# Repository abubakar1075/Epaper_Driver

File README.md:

# CanvasBT — EPaper BLE Image Transfer System

An end-to-end, practical reference for sending images to a 6‑color e‑paper display over Bluetooth Low Energy (BLE). This repo combines:
- Flutter mobile app (select/process image, send over BLE)
- ESP32/Arduino firmware (receive, persist, and render to e‑paper)
- Python tools (desktop image conversion and BLE utilities)

## Educational Intent

This is a personal, non‑commercial project published publicly to help engineers and learners understand mobile ↔ BLE ↔ embedded firmware ↔ e‑paper display integration. It focuses on real constraints: BLE throughput, MTU/chunking, limited RAM, image quantization, and e‑paper refresh behavior.

## What You’ll Learn

- Designing a BLE data transfer flow from mobile to microcontroller
- Handling chunking, buffering, acknowledgments, and integrity checks
- Converting images to a 6‑color e‑paper format (quantization + optional dithering)
- Structuring firmware for display initialization, frame buffer handling, and refresh sequencing
- Organizing a multi‑component system repo for reproducibility

## System Overview

Flutter App → (BLE) → ESP32 Firmware → (SPI/GPIO) → 6‑Color E‑Paper Display

Typical workflow:
1. Choose an image in the Flutter app
2. Enhance and quantize to hardware palette (optionally dither)
3. Pack pixels and transfer over BLE in chunks
4. ESP32 reassembles the image payload and persists if needed
5. ESP32 renders to e‑paper and triggers a refresh

## Repository Structure

- [Flutter/](Flutter/) — Mobile app with all UI + BLE + image logic
	- Core files: [lib/main.dart](Flutter/lib/main.dart), [lib/ble_manager.dart](Flutter/lib/ble_manager.dart), [lib/image_processor.dart](Flutter/lib/image_processor.dart)
	- Platforms: [android/](Flutter/android/), [ios/](Flutter/ios/), [windows/](Flutter/windows/), [linux/](Flutter/linux/), [macos/](Flutter/macos/), [web/](Flutter/web/)
	- Assets/examples: [Framepic/](Framepic/), [SamplePics/](SamplePics/), [EmulatorScreenshots/](EmulatorScreenshots/)
- [Arduino/Spectra6/](Arduino/Spectra6/) — ESP32 firmware and display drivers
	- Key files: [Spectra6.ino](Arduino/Spectra6/Spectra6.ino), [BLE.cpp](Arduino/Spectra6/BLE.cpp), [SPICom.cpp](Arduino/Spectra6/SPICom.cpp), [W21.cpp](Arduino/Spectra6/W21.cpp)
	- Build artifacts (example boards): [build/esp32.esp32.dfrobot_firebeetle2_esp32e/](Arduino/Spectra6/build/esp32.esp32.dfrobot_firebeetle2_esp32e/)
- [Python/](Python/) — Desktop tools: [epd_image_tool.py](Python/epd_image_tool.py), [epd_image_tool_ble.py](Python/epd_image_tool_ble.py)
- Documentation: [USER_MANUAL.md](USER_MANUAL.md), project notes in [.github/copilot-instructions.md](.github/copilot-instructions.md)

## Hardware Requirements

- ESP32 development board (tested on FireBeetle2 ESP32‑E and similar)
- 6‑color e‑paper display, 800×480 (landscape)
- SPI wiring: MOSI, SCLK, CS; control pins: DC, RST, BUSY; power: VCC, GND
- Optional touch/wake input

Tip: Pin mapping varies by display/module; check the firmware for pin defines and adapt wiring accordingly.

### Wiring & Connections

SPI and control signals required:

- Data/Clock: MOSI, SCLK
- Select: CS
- Control: DC (data/command), RST (reset), BUSY (controller busy)
- Power: VCC, GND

Example pin mapping template (fill with your board pins):

| Signal | ESP32 Pin | Notes |
|--------|-----------|-------|
| MOSI   | GPIO XX   | SPI data out |
| SCLK   | GPIO XX   | SPI clock |
| CS     | GPIO XX   | Chip select |
| DC     | GPIO XX   | Data/Command select |
| RST    | GPIO XX   | Hardware reset |
| BUSY   | GPIO XX   | Display busy (input to ESP32) |
| VCC    | 3V3       | Stable 3.3V |
| GND    | GND       | Common ground |

ESD and power tips:
- Keep SPI lines short and tidy; use ground reference next to signal lines where possible.
- Ensure 3.3V supply is robust; brownouts cause BLE drops or partial refreshes.
- Use level‑compatible displays; do not drive 5V logic into the panel.

## Software Requirements

- Flutter SDK (stable), Android Studio or VS Code
- Android phone recommended for BLE testing
- Arduino IDE with ESP32 board support; ArduinoBLE library
- Python 3.9+ (virtual environment recommended)

## Getting Started

### Flutter App

```bash
cd Flutter
flutter pub get
flutter run
```

Notes:
- Requires a BLE‑capable Android device connected via USB (or emulator with suitable BLE proxies).
- The app scans for devices with “EPD” in the advertisement name.

Quick architecture diagram:

```
┌────────────┐      BLE      ┌──────────────┐    SPI/GPIO    ┌─────────────────┐
│  Flutter   │ ───────────▶  │   ESP32      │ ─────────────▶ │  E‑Paper Panel  │
│   (App)    │ ◀───────────  │  (Firmware)  │ ◀───────────── │  (6‑Color, 800×480)
└────────────┘  Status/ACK   └──────────────┘   Busy/Control └─────────────────┘
```

### Arduino Firmware (ESP32)

1. Open the firmware in Arduino IDE: [Arduino/Spectra6/Spectra6.ino](Arduino/Spectra6/Spectra6.ino)
2. Install and select your ESP32 board package.
3. Ensure required libraries (ArduinoBLE, SPI, FS/SPIFFS) are available.
4. Build and upload to your ESP32.

After flashing:
- The device advertises over BLE (e.g., name includes “EPD”).
- Battery percentage is sent on connection.
- Deep sleep is used for low power; touch wake is supported.

### Python Tools (Optional/Desktop)

```bash
cd Python
python epd_image_tool.py --help
python epd_image_tool_ble.py --help
```

Examples:

```bash
# Standalone image conversion
python epd_image_tool.py --input SamplePics/photo.jpg --output out.bin

# BLE transfer from desktop (development aid)
python epd_image_tool_ble.py --file out.bin
```

## Display + Image Processing

- Display resolution: 800×480
- Pixels packed at 2 pixels per byte (palette index nibble pairs)
- Optional 180° rotation supported for orientation

Hardware palette (critical for compatibility):

```dart
static const List<ColorMap> hwPalette = [
	ColorMap(0x00, Color.fromRGBO(0, 0, 0, 1)),       // Black
	ColorMap(0xFF, Color.fromRGBO(255, 255, 255, 1)), // White  
	ColorMap(0xFC, Color.fromRGBO(255, 255, 0, 1)),   // Yellow
	ColorMap(0xE0, Color.fromRGBO(210, 0, 0, 1)),     // Red
	ColorMap(0x03, Color.fromRGBO(0, 0, 180, 1)),     // Blue
	ColorMap(0x1C, Color.fromRGBO(0, 150, 0, 1)),     // Green
];
```

Pipeline: Load → Enhance (brightness/contrast/saturation) → Resize (fit/stretch) → Quantize to 6 colors (optional Floyd‑Steinberg) → Pack pixels → Optional rotation → BLE transfer.

### Image Packing Format

- Two pixels per byte: `hi_nibble = pixel0_index`, `lo_nibble = pixel1_index`.
- Palette index must match the hardware palette order shown above.
- Row ordering follows the chosen orientation; rotation is applied pre‑transfer when enabled.

## BLE Protocol

- Service: Nordic UART `6E400001-B5A3-F393-E0A9-E50E24DCCA9E`
- Transfer types: `0x10` image, `0x20` OTA update
- Handshake: 4‑byte size header → ACK → chunked data
- Acknowledgments: `0x01` (size received), `0x02` (progress), `0x03` (complete), `0xFF` (error)
- Battery status: `0xB0` + percentage byte on connection
- Chunk size: 480 bytes (optimized for MTU and reliability)

Device discovery: the app scans for advertisements containing “EPD”.

### Packet/Handshake Details

Header exchange (image or OTA):
- Mobile sends 4‑byte size header (little‑endian length of payload) and transfer type byte (`0x10` image, `0x20` OTA).
- ESP32 replies with ACK `0x01` to confirm size reception.

Chunk transfer:
- Mobile streams payload in 480‑byte chunks.
- ESP32 issues periodic progress ACK `0x02` (implementation‑dependent cadence).
- On completion, ESP32 replies `0x03` or `0xFF` on error.

Battery status:
- On connection, ESP32 sends `0xB0` followed by a single percentage byte.

Recommended reliability notes:
- If MTU is smaller or unstable, reduce chunk size or increase ACK cadence.
- Consider adding sequence numbers and CRC in future (see Roadmap) for stronger integrity.

### Transfer Flow (ASCII)

```
App                                  ESP32
───                                  ────
Connect BLE  ───────────────────────▶ Advertise "EPD"
Receive 0xB0% ◀────────────────────── Battery status
Send header(size,type) ─────────────▶
					 ◀────────────── 0x01 (size ACK)
Send chunks (480B × N) ─────────────▶
					 ◀────────────── 0x02 (progress)
End of chunks ──────────────────────▶
					 ◀────────────── 0x03 (complete) or 0xFF (error)
```

OTA follows the same flow with type `0x20`, writing to firmware/image storage as defined in the ESP32 code.

## App Architecture & State

- Monolithic learning app with UI in [lib/main.dart](Flutter/lib/main.dart)
- BLE communication handled in [lib/ble_manager.dart](Flutter/lib/ble_manager.dart)
- Image processing in [lib/image_processor.dart](Flutter/lib/image_processor.dart)
- `setState()` used for state updates; BLE connection state tracked with timers
- Image library cached in memory and persisted via JSON/local storage
- Gestures: pan/zoom/rotate for precise framing

### UI/UX Flow Chart (Simplified)

```
[Launch]
	│
	├─▶ [Scan BLE] ─▶ [Select Device] ─▶ [Connect]
	│                                  │
	│                                  └─▶ [Battery %] overlay
	│
	├─▶ [Pick Image] ─▶ [Frame (pan/zoom/rotate)] ─▶ [Enhance]
	│                                                     │
	│                                                     └─▶ [Quantize + Pack]
	│                                                                     │
	└────────────────────────────────────────────────────────────────────▶ [Send]
																								  │
																								  └─▶ [Progress + Speed]
																											│
																											└─▶ [Complete → Refresh]
```

## Performance & Debugging

- High‑speed BLE: tuned chunk size (480 bytes) and batched ACKs
- Background isolates for image conversion to keep UI responsive
- Extensive console logging across Flutter and Arduino
- Real‑time transfer speed display during BLE operations
- Automatic reconnection attempts on disconnection

### Tips
- Enable verbose logs in both app and firmware to diagnose MTU and timing issues.
- Use a BLE scanner app to verify advertisement and connection parameters.
- When tuning throughput, adjust connection interval and preferred PHY (if supported by device).

## Troubleshooting

- If BLE MTU negotiation is limited, transfers fall back gracefully; reducing chunk size improves reliability.
- Ensure the ESP32 is powered adequately; weak power can cause BLE drops or SPI timing issues.
- For slow refresh: 6‑color e‑paper refresh is inherently slower; this is expected.
- On Android, grant Bluetooth, location, and storage permissions if prompted.

Common issues and remedies:
- Garbled image: verify palette index mapping and packing (2 pixels/byte).
- Partial frame update: ensure the firmware processes the full payload before refresh; check `BUSY` handling.
- Frequent BLE disconnects: check power supply, antenna orientation, and reduce chunk size.
- Very slow refresh: expected for multi‑color e‑paper; consider pre‑processing to reduce transitions.

## Roadmap (Optional)

- Add CRC/integrity verification and retry strategy
- Improve compression to reduce transfer time
- iOS testing and notes
- Wiring diagram, pin mapping table, and hardware photos
- docs/ARCHITECTURE.md with packet diagrams and flow

Additional ideas:
- Add ASCII timing diagrams for SPI transfers.
- Provide pin mapping examples per board (FireBeetle2, ESP32‑WROOM, etc.).
- Export PNG diagrams into a `docs/` folder for quick reference.

## Contributing

Contributions are welcome:
- Fork the repo
- Create a feature branch
- Open a pull request with a clear description

## Security

Do not commit credentials, tokens, or private keys. If you discover a security issue, please open an issue describing it at a high level.

## License

Recommended: MIT License (permissive). If you’d like to adopt it, add a `LICENSE` file at the repo root.

## Author

Abu Bakar — Embedded Systems Engineer (UK)
GitHub: https://github.com/abubakar1075

## See Also

- Mobile app source and docs: [Flutter/](Flutter/)
- Firmware and hardware integration: [Arduino/Spectra6/](Arduino/Spectra6/)
- Desktop tooling: [Python/](Python/)
- User guide: [USER_MANUAL.md](USER_MANUAL.md)

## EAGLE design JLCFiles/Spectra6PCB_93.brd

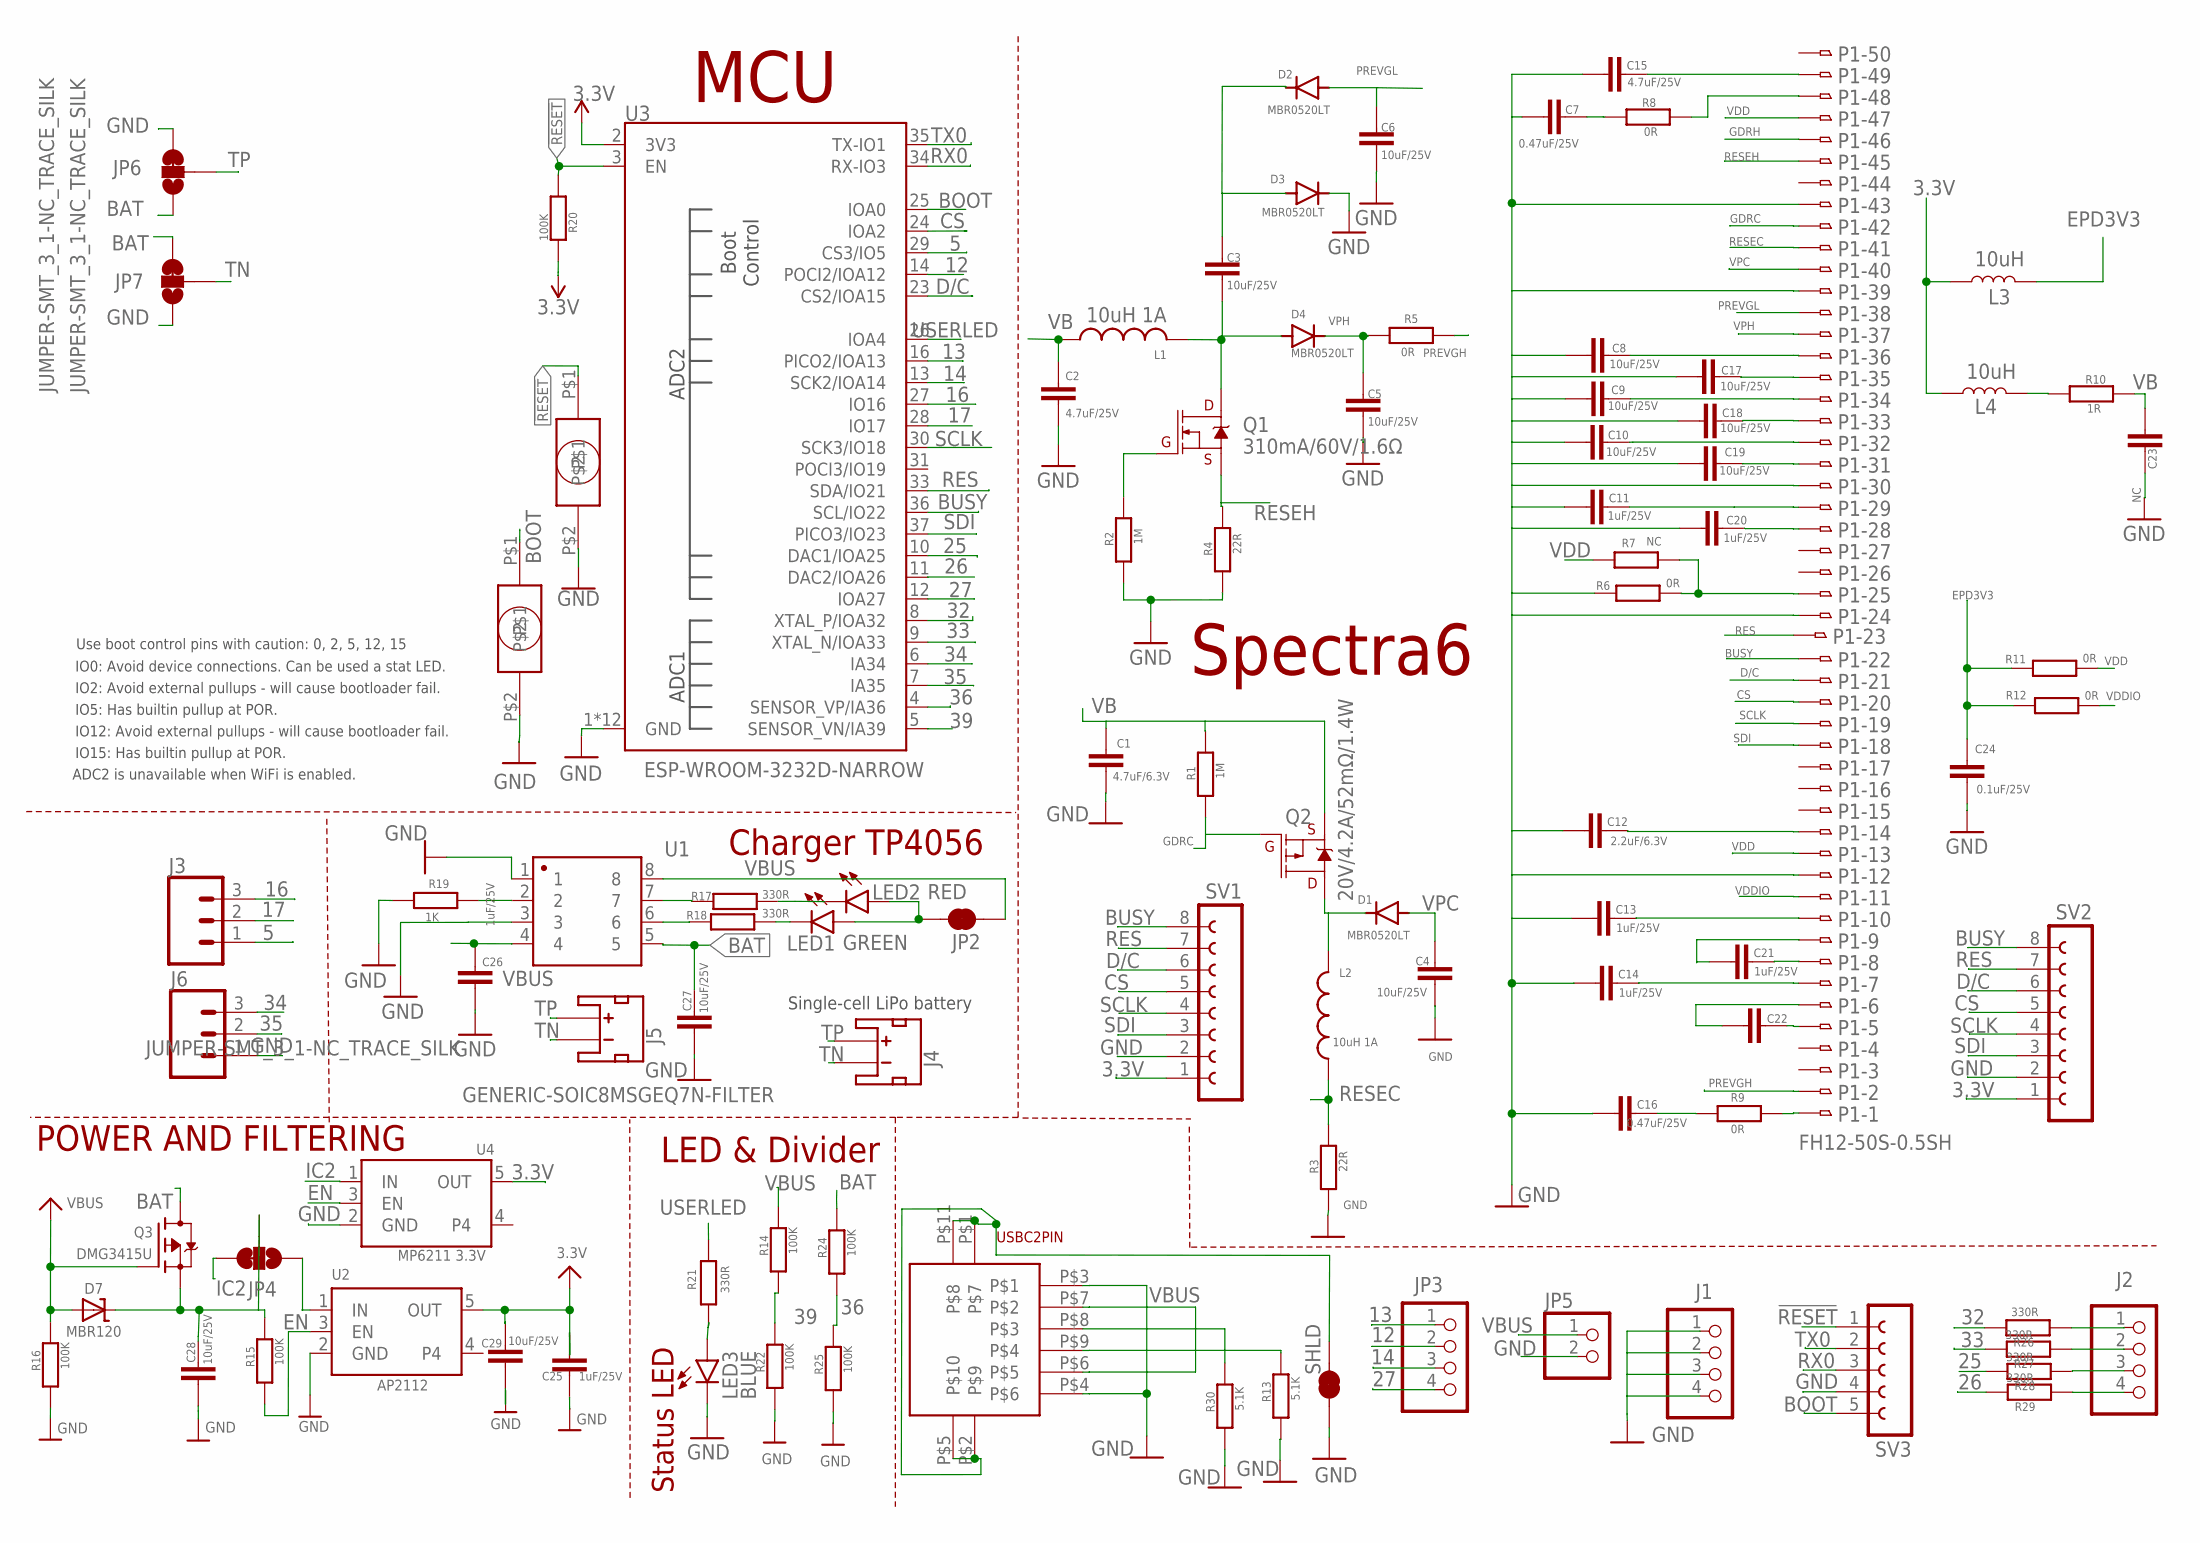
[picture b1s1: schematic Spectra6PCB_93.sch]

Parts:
C1: 4.7uF/6.3V; C0805
C2, C15: 4.7uF/25V; C0805
C3, C4, C5, C6, C8, C9, C10, C17, C18, C19, C27, C28, C29: 10uF/25V; C0805
C7, C16: 0.47uF/25V; C0805
C11, C13, C14, C20, C21, C22, C25, C26: 1uF/25V; C0805
C12: 2.2uF/6.3V; C0805
C23: NC; C0805
C24: 0.1uF/25V; C0805
D1, D2, D3, D4: MBR0520LT; SOD123
D7: MBR120; SOD-123
J1, J2: PINHD-1X4; 1X04
J3, J6: CONN_03PAD; 1X03_SOLDER_PADS
J4: JST_2MM_MALE; JST-2-SMD
J5: NC; JST-2-SMD
JP2: JUMPER-SMT_2_NC_TRACE_SILK; SMT-JUMPER_2_NC_TRACE_SILK
JP3: PINHD-1X4; 1X04
JP4, JP6, JP7: JUMPER-SMT_3_1-NC_TRACE_SILK; SMT-JUMPER_3_1-NC_TRACE_SILK
JP5: PINHD-1X2; 1X02
L1, L2: 10uH 1A; L4035M
L3, L4: 10uH; 0805
LED1: GREEN; SML0805
LED2: RED; SML0805
LED3: BLUE; SML0805
P1: FH12-50S-0.5SH
Q1: 310mA/60V/1.6Ω; SOT323
Q2: 20V/4.2A/52mΩ/1.4W; SOT23-3
Q3: DMG3415U; SOT23-R
R1, R2: 1M; M0805
R3, R4: 22R; M0805
R5, R6, R8, R9, R11, R12: 0R; M0805
R7: NC; M0805
R10: 1R; M0805
R13, R30: 5.1K; M0805
R14, R15, R16, R20, R22, R24, R25: 100K; M0805
R17, R18, R21, R26, R27, R28, R29: 330R; M0805
R19: 1K; M0805
S3, S4: TACTILE
SHLD: SHLD; SMT-JUMPER_2_NC_TRACE_NO-SILK
SV1, SV2: FE08-1; FE08
SV3: FE05-1
U1: GENERIC-SOIC8MSGEQ7N-FILTER; SO08
U2: AP2112; SOT23-5
U3: ESP-WROOM-3232D-NARROW; ESP-WROOM-32D-NARROW
U4: MP6211 3.3V; SOT23-5
U$4: USBC6PIN

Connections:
3.3V: C25.2, C29.2, L3.1, L4.1, R20.2, SV1.1, SV2.1, U2.5 (OUT), U3.2 (3V3), U4.5 (OUT)
5: J3.1, U3.29 (CS3/IO5)
12: JP3.2, U3.14 (POCI2/IOA12)
13: JP3.1, U3.16 (PICO2/IOA13)
14: JP3.3, U3.13 (SCK2/IOA14)
16: J3.3, U3.27 (IO16)
17: J3.2, U3.28 (IO17)
25: R28.2, U3.10 (DAC1/IOA25)
26: R29.2, U3.11 (DAC2/IOA26)
27: JP3.4, U3.12 (IOA27)
32: R26.2, U3.8 (XTAL_P/IOA32)
33: R27.2, U3.9 (XTAL_N/IOA33)
34: J6.3, U3.6 (IA34)
35: J6.2, U3.7 (IA35)
36: R24.1, R25.2, U3.4 (SENSOR_VP/IA36)
39: R14.1, R22.2, U3.5 (SENSOR_VN/IA39)
!RESET!: R20.1, S4.P$1, SV3.1, U3.3 (EN)
BAT: C27.2, JP6.1, JP7.3, Q3.3 (D), R24.2, U1.5
BOOT: S3.P$1, SV3.5, U3.25 (IOA0)
BUSY: P1.22, SV1.8, SV2.8, U3.36 (SCL/IO22)
CS: P1.20, SV1.5, SV2.5, U3.24 (IOA2)
D/C: P1.21, SV1.6, SV2.6, U3.23 (CS2/IOA15)
EN: R15.1, U2.3 (EN), U4.3 (EN)
EPD3V3: C24.2, L3.2, R11.1, R12.1
GDRC: P1.42, Q2.1 (G), R1.1
GDRH: P1.46, Q1.1 (G), R2.2
GND: C1.1, C2.1, C4.1, C5.2, C6.2, C7.1, C8.1, C9.1, C10.1, C11.1, C12.1, C13.1, C14.1, C15.1, C16.1, C17.1, C18.1, C19.1, C20.1, C23.2, C24.1, C25.1, C26.1, C27.1, C28.1, C29.1, D3.C, J1.1, J1.2, J1.3, J1.4, J6.1, JP5.2, JP6.3, JP7.1, LED3.C, P1.24, P1.30, P1.39, P1.43, R2.1, R3.1, R4.1, R6.1, R13.1, R16.1, R19.1, R22.1, R25.1, R30.1, S3.P$2, S4.P$2, SHLD.1, SV1.2, SV2.2, SV3.4, U1.1, U1.3, U2.2 (GND), U3.1 (GND), U3.15 (GND), U3.38 (GND), U3.GND1 (GND), U3.GNDT1 (GND), U3.GNDT2 (GND), U3.GNDT3 (GND), U3.GNDT4 (GND), U3.GNDT5 (GND), U3.GNDT6 (GND), U3.GNDT7 (GND), U3.GNDT8 (GND), U4.2 (GND), U$4.P$3, U$4.P$4
IC2: JP4.3, U4.1 (IN)
LED1: LED2.C, R17.2
LED2: LED1.C, R18.2
unnamed: C15.2, P1.49
unnamed: P1.48, R8.2
unnamed: C7.2, R8.1
unnamed: L4.2, R10.1
unnamed: C8.2, P1.36
unnamed: C17.2, P1.35
unnamed: C9.2, P1.34
unnamed: C18.2, P1.33
unnamed: C10.2, P1.32
unnamed: C19.2, P1.31
unnamed: C11.2, P1.29
unnamed: C20.2, P1.28
unnamed: P1.25, R6.2, R7.2
unnamed: JP2.2, LED1.A, LED2.A
unnamed: C12.2, P1.14
unnamed: C13.2, P1.10
unnamed: C21.1, P1.9
unnamed: C21.2, P1.8
unnamed: C14.2, P1.7
unnamed: C22.1, P1.6
unnamed: C22.2, P1.5
unnamed: P1.1, R9.2
unnamed: C16.2, R9.1
unnamed: C3.2, D4.A, L1.2, Q1.3 (D)
unnamed: C3.1, D2.C, D3.A
unnamed: J2.1, R26.1
unnamed: J2.2, R27.1
unnamed: D1.C, L2.2, Q2.3 (D)
unnamed: J2.3, R28.1
unnamed: C1.2, Q2.2 (S), R1.2
unnamed: R19.2, U1.2
unnamed: JP4.1, U2.1 (IN)
unnamed: C28.2, D7.C, JP4.2, Q3.2 (S), R15.2
unnamed: R18.1, U1.6
unnamed: R17.1, U1.7
unnamed: LED3.A, R21.1
unnamed: J2.4, R29.1
unnamed: R13.2, U$4.P$9
unnamed: R30.2, U$4.P$8
PREVGH: P1.2, R5.2
PREVGL: C6.1, D2.A, P1.38
RES: P1.23, SV1.7, SV2.7, U3.33 (SDA/IO21)
RESEC: L2.1, P1.41, R3.2
RESEH: P1.45, Q1.2 (S), R4.2
RX0: SV3.3, U3.34 (RX-IO3)
SCLK: P1.19, SV1.4, SV2.4, U3.30 (SCK3/IO18)
SDI: P1.18, SV1.3, SV2.3, U3.37 (PICO3/IO23)
SHLD: SHLD.2, U$4.P$1, U$4.P$2, U$4.P$5, U$4.P$11
TN: J4.1 (-), J5.1 (-), JP7.2
TP: J4.2 (+), J5.2 (+), JP6.2
TX0: SV3.2, U3.35 (TX-IO1)
USERLED: R21.2, U3.26 (IOA4)
VB: C2.2, C23.1, L1.1, R10.2
VBUS: C26.2, D7.A, JP2.1, JP5.1, Q3.1 (G), R14.2, R16.2, U1.4, U1.8, U$4.P$6, U$4.P$7
VDD: P1.13, P1.47, R7.1, R11.2
VDDIO: P1.11, R12.2
VPC: C4.2, D1.A, P1.40
VPH: C5.1, D4.C, P1.37, R5.1

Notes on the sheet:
Single-cell LiPo battery
POWER AND FILTERING
IO0: Avoid device connections. Can be used a stat LED.
ADC2 is unavailable when WiFi is enabled.
IO12: Avoid external pullups - will cause bootloader fail.
Use boot control pins with caution: 0, 2, 5, 12, 15
IO2: Avoid external pullups - will cause bootloader fail.
IO15: Has builtin pullup at POR.
IO5: Has builtin pullup at POR.
Status LED
LED & Divider
Spectra6
MCU
Charger TP4056

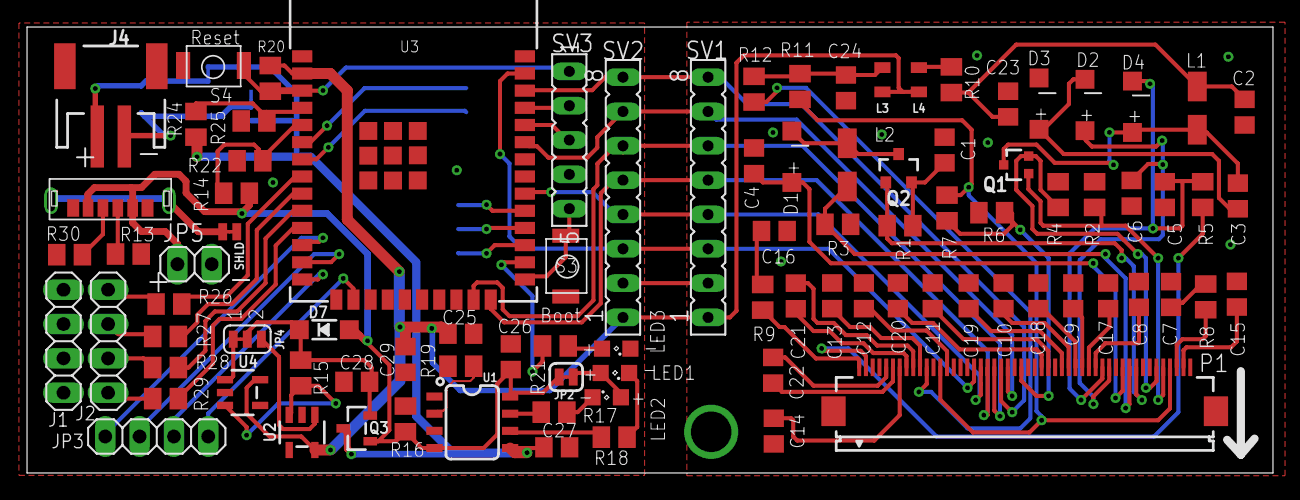
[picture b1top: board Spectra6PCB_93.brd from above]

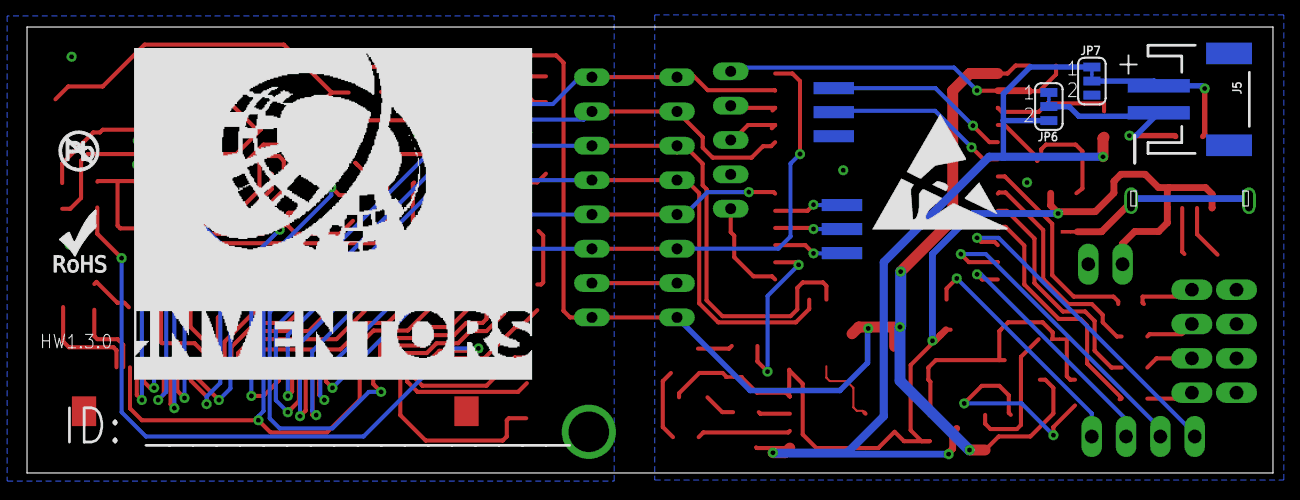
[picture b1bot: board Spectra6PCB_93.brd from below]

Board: 2 copper layers, 92.2 x 33.0 mm, 100 parts (8 on the bottom side), 88 nets.

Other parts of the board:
U$5: ROHS_LOGO_0.18_IN
U$7: NO_PB_LOGO_0.120
U$8: ESD_10.00

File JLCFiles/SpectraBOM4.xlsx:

Comment | Designator | FootPrint | JLCPCB
NC | FEMALE SV1
0.1uF/50V | C24 | C0805 | C49678
0.47uF/50V | C7, C16 | C0805 | C13967
0R | R5, R6, R8, R9, R11, R12 | M0805 | C17477
10uF/25V | C3, C4, C5, C6, C8, C9, C10, C17, C18, C19 | C0805 | C15850
10uH 1A | L1, L2 | L4035M | C6364790
1M | R1, R2 | M0805 | C17514
1R | R10 | M0805 | C25271
1uF/50V | C11, C13, C14, C20, C21, C22 | C0805 | C28323
2.2uF/25V | C12 | C0805 | C19110
20V/4.2A/52mΩ/1.4W | Q2 | SOT23-3 | C10487
0.22ohm | R3, R4 | M0805 | C149646
N Channel Mospet | Q1 | SOT323 | C7603347
4.7uF/25V | C1, C2, C15 | C0805 | C1779
FH12-50S-0.5SH | P1 | FH12-50S-0.5SH | C202116
120Ω@100MHz | L3, L4 | 805.0 | C79382
MBR0530 | D1, D2, D3, D4 | SOD123 | C77336
NC | C23 | C0805
NC | R7 | M0805
Controller
NC | J3, J6 | Multi
NC | SV2 FEMALE
JST_2MM_MALE | J4 | JST | C295747
NC | JP5 PIN
NC | J1, J2, JP1, JP3 | PIN
100K | R14, R15, R16, R20, R22, R24, R25 | M0805 | C149504
10uF/25V | C27, C28, C29 | C0805 | C15850
1K | R19 | M0805 | C17513
1uF/50V | C25, C26 | C0805 | C28323
330R | R17, R18, R26, R27, R28, R29, R21 | M0805 | C17630
5.1K | R13, R30 | M0805 | C27834
AP2112 | U2 | SOT23-5 | C51118
DMG3415U | Q3 | SOT23-R | C96616
ESP-WROOM-32E | U3 | ESP-WROOM-32D-NARROW | C701342
TP4056 | U1 | SO08 | C16581
GREEN | LED1 | SML0805 | C2297
YELLOW | LED3 | SML0805 | C2296
NC | JP2 | SMT-JUMPER_2_NC_TRACE_SILK
NC | JP4 | SMT-JUMPER_3_1-NC_TRACE_SILK
MBR120 | D7 | SOD-123 | C223608
ME6211 3.3V | U4 | SOT23-5 | C82942
NC | J5 | JST-2-SMD
RED | LED2 | SML0805 | C84256
Reset/Boot | S3, S4 | MOMENTARY-SWITCH-SPST-SMD-4x3 | C720477
NC | SHLD | SMT-JUMPER_2_NC_TRACE_NO-SILK
USBC6PIN | U$4 | USBC6PIN | C30167341
NC | JST

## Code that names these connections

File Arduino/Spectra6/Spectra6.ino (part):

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#include "BLE.h"
void handleLedBlinking();
// LED aliases for readability
const int pcbLED = LED2;   // board LED (e.g., GPIO4 on FirstPCB)
const int userLED = 26;    // user LED on GPIO32 (mirrors pcbLED)

// ============================
// LittleFS image slot management
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    }
    // Ensure EPD pins and SPI are initialized before driving the display
    pinMode(PIN_EPD_BUSY, INPUT);  // BUSY (panel drives this)
    pinMode(PIN_EPD_RST, OUTPUT);  // RES
    pinMode(PIN_EPD_DC, OUTPUT);   // DC  
    pinMode(PIN_EPD_CS, OUTPUT);   // CS  
    digitalWrite(PIN_EPD_CS, HIGH); // deselect
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
  pinMode(GND, OUTPUT); // Will be ignored if GPIO35 is input-only
  pinMode(pcbLED, OUTPUT); // LED on GPIO4
  pinMode(userLED, OUTPUT);   // Mirror LED on GPIO32
  digitalWrite(GND, LOW);
  analogWrite(pcbLED, 255);
  analogWrite(userLED, 255);
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  if (!hardwareInitializedOnWake) {
    // Initialize EPD pins - but don't run any display commands yet
    pinMode(PIN_EPD_BUSY, INPUT);  // BUSY (panel drives this)
    pinMode(PIN_EPD_RST, OUTPUT);  // RES
    pinMode(PIN_EPD_DC, OUTPUT);   // DC  
    pinMode(PIN_EPD_CS, OUTPUT);   // CS  
    digitalWrite(PIN_EPD_CS, HIGH); // deselect
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      int batteryRaw = analogRead(BATTERY_PIN);
      float batteryAdcVoltage = (batteryRaw / 4095.0) * 3.3;
      float batteryVoltage = batteryAdcVoltage * 2.0;
      Serial.printf("[stopingSleep] Holding awake | Touch:%u | usb:%.2fV | bat:%.2fV\n", t, usbVoltage, batteryVoltage);
    }

    delay(10);
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
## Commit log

2025-08-23 FirstOne
2025-08-23 ColoredImages
2025-08-24 SaperateWindows
2025-08-24 FrameAdded
2025-08-24 BetterResults
2025-08-24 ZoomInZoomOutFix
2025-08-24 VerticalOptionAdded
2025-08-24 VerticalInProcessed
2025-08-24 VerticalInFrameToo
2025-08-25 SomeOptionsAdded
2025-08-25 CleanVersion
2025-08-25 LibraryAdded
2025-08-25 FlickeringFixed
2025-08-25 LibraryModification
2025-08-26 SmallFixes
2025-08-26 AutoConnect
2025-08-26 CleanCode
2025-08-26 LibraryImagesAdded
2025-08-26 4ImagesModification
2025-08-27 ImagesChanged
2025-09-16 ImageFlipped
2025-09-17 logoAdded
2025-09-17 Name
2025-09-17 BLEConnection
2025-09-17 BLEConnection2
2025-09-17 ButtonNameChanges
2025-09-17 TuneOptionRemoved
2025-09-17 SmoothCropping
2025-09-17 SmoothCropping2
2025-09-17 BorderAdded
2025-09-17 WhiteBorderAdded
2025-09-17 connectionStatusAdded
2025-09-17 AutoSearchBLE
2025-09-17 Auto connect
2025-09-18 eframeTopAdded
2025-09-18 eframeFitted
2025-09-18 FirstWindowFixes
2025-09-18 TabArrangments
2025-09-18 ConnStatusRemoved
2025-09-18 portrait/Landscape
2025-09-18 GallaryImage
2025-09-18 GallaryPortraitFix
2025-09-18 StatusInOneLine
2025-09-18 AiImageGeneration
2025-09-18 AIColourfulImage
2025-09-18 Pixel Isse fixed
2025-09-18 RenameToLibrary
2025-09-18 SendButtonFix
2025-09-18 buttonArrangement
2025-09-18 RefreshButtonMoved
2025-09-18 InframeSetting
2025-09-18 InframeSetting2
2025-09-18 SendbuttonAlwaysEnable
2025-09-18 ImageOnSend
2025-09-18 FirstWindowDeleted
2025-09-18 InframeFix
2025-09-18 AIImagePromptChange
2025-09-18 AiImageWindowChanges
2025-09-19 FrameBorder
2025-09-19 BluetoothMessageChanged
2025-09-19 Landscape/BluetoothOption
2025-09-19 SearchPromptChange
2025-09-19 SpellCorrection
2025-09-19 LandscapeOptionEnable
2025-09-19 CanvasBT
2025-09-19 Images Changed
2025-09-24 ArduinoCodeUpdated
2025-09-24 BatteryStatusAdded
2025-09-24 AppRename
2025-09-25 FirstLibraryImage
2025-09-25 LibraryImageOrientation
2025-09-25 ImageFixed
2025-09-27 PortrateMode
2025-09-27 APKGenerated
2025-09-27 ImageAccordingtoFrame
2025-10-10 ArduinoFilesUpdated
2025-10-11 ArduinoFolderNameAdded
2025-10-11 BinFileAdded
2025-10-11 BoardSelection
2025-10-11 T_fileReceving
2025-10-12 WorkingOTA
2025-10-12 After_OTA
2025-10-12 OTABugFix
2025-10-12 AutoOTAFix
2025-10-12 HIghSpeed
2025-10-12 AnotherSmallFix
2025-10-12 ErrorFixed
2025-10-13 __FileStructure__
2025-10-13 __FileStructure2__
2025-10-13 JLCFilesAdded
2025-10-13 OnlineImage
2025-10-13 GoogleImages
2025-10-13 Fast Images
2025-10-13 ButtonSize
2025-10-13 ButtonsUpdate
2025-10-13 ButtonFix2
2025-10-13 BackgroundFit
2025-10-13 BackgroundImproved
2025-10-13 BackgroundImage
2025-10-13 ButtonEnabled
2025-10-13 ButtonFixed
2025-10-13 ButtonFixed2
2025-10-13 OnlineButton
2025-10-13 OnlineButtonFix2
2025-10-13 A_TouchLED
2025-10-14 A_autoThreshold
2025-10-18 F_response:false
2025-10-18 A_SleepAnyway
2025-10-18 A_SPIFFSClean
2025-10-19 AS_StableVersion
2025-10-19 F_OnlineImage
2025-10-19 F_Better
2025-10-19 F_smallChange
2025-10-19 AF_AutoOTA
2025-10-19 FA_AutoOTA2
2025-10-19 F_OTAbuttonHide
2025-10-19 A_PrintVersion
2025-10-19 F_FlikerSolved
2025-10-19 A_BatteryAdj
2025-10-19 F_CanvasBTImageChanged
2025-10-19 F_Small button fix
2025-10-21 A_BatteryAvg
2025-10-21 A_BatteryAdjucement
2025-10-21 F_DiscoveringServiveFix
2025-10-21 F_ExcetionHandeled
2025-10-24 A_TerminalCommands
2025-10-24 A_TapsDetected
2025-10-24 A_PCBMCU
2025-10-24 A_3Images
2025-10-24 A_cleanCommand
2025-10-24 A_30sOn
2025-10-24 A_AllTimeBLE
2025-10-27 F_foldernameChanged
2025-10-27 F_Build
2025-10-27 A_BatGPIOChanged
2025-10-27 A_2LEDsForStstus
2025-10-27 A_5 Images
2025-10-27 A_CalButtonChange
2025-10-27 Stable
2025-10-27 F_ImageRotated
2025-10-28 F_Apk
2025-10-29 F_LandAndPortrateFix
2025-10-30 F_SimplifiedApproch
2025-10-30 flutterpubget
2025-10-30 F_logoChanged
2025-10-30 F_InAppImageChange
2025-10-30 F_buttonSwapped
2025-10-30 F_buttonsRename
2025-10-30 F_FingerPositionChnaged
2025-10-30 F_AIPromptChanged
2025-10-30 F_SavedIconChanged
2025-10-30 ImageSlidingFixed
2025-10-30 F_AutomaticOrientation
2025-10-30 F_MoreStable
2025-10-30 F_ImageImportImproved
2025-10-30 F_FlickerReduce
2025-11-03 F_Release
2025-11-03 A_NoCurruptImage
2025-11-04 F_BackgroundandInAppLogo
2025-11-05 A_Longpress
2025-11-05 A_QuickSleep
2025-11-05 AF_Verions
2025-11-05 PCB_100units
2025-11-08 A_DebugDataOnterminal
2025-11-08 A_SmoothSending
2025-11-08 A_SPIFFSReadWriteLogs
2025-11-08 A_SpiffSizeCompDeleteImage
2025-11-08 A_Stable
2025-11-08 A_sizeImproved
2025-11-08 AF_OTAFormate
2025-11-09 A_KeepThresholdSafe
2025-11-09 A_2Formates
2025-11-09 A_APK
2025-11-10 F_pixaby
2025-11-10 F_200Images
2025-11-10 F_catagoriesAdded
2025-11-10 F_Improved
2025-11-10 F_ScrollingRmoved
2025-11-10 F_splashlogo
2025-11-10 F_littleAdjustment
2025-11-10 F_pixabayRemoved
2025-11-10 A_APKAgain
2025-11-11 A_LittleFS
2025-11-11 A_imageDeleting
2025-11-11 A_ProperImageSwitch
2025-11-11 A_ChargingLEDandWakeup
2025-11-11 A_LEDPWMFIX
2025-11-11 LanFix
2025-11-11 AF_BatteryChargingStatus
2025-11-11 A_ButtonPressedFormate
2025-11-11 F_searchandNumber
2025-11-11 F_FrameAdjustment
2025-11-11 F_FrameAdjusment2
2025-11-11 F_ImagesRename
2025-11-11 F_ImagesPlaced
2025-11-11 F_savedEditor
2025-11-12 F_ProperNaming
2025-11-12 F_PixabyNameRemoved
2025-11-12 F_alndscape/portrateFix
2025-11-12 F_SlidingImageFix
2025-11-12 F_PixabayImageOrientation
2025-11-12 f_Informationbutton
2025-11-12 F_3barButton
2025-11-12 F_3buttonAppIcon
2025-11-12 F_HowToUse
2025-11-12 F_Error Fix
2025-11-12 F_smallFix
2025-11-12 A_ReleaseAfterLongTouch
2025-11-12 AF_TouchCalibration
2025-11-12 AF_FirmwareandLEDFix
2025-11-13 AF_BinAndAPK
2025-11-13 F_BLEInDebug
2025-11-13 F_RemovedPreInstalledImages
2025-11-13 F_SavedImageNotRotating
2025-11-13 F_orientationFix
2025-11-13 F_NamingConventions
2025-11-13 F_Simple
2025-11-13 F_ImageAtCenter
2025-11-13 F_CropeframeAdjustment
2025-11-13 F_1SavedImage
2025-11-13 F_ErrorFix
2025-11-13 F_SmoothImage
2025-11-13 F_textSimplify
2025-11-13 F_SavedImage
2025-11-13 F_Fix
2025-11-13 F_LittleFix
2025-11-13 F_frameFiix
2025-11-15 F_LandscapeReset
2025-11-15 F_potrateImageSet
2025-11-15 F_ImageOrientationFix
2025-11-15 F_GoodQualityImage
2025-11-15 F_Pixabay
2025-11-15 F_MessagesImproved
2025-11-15 AF_BateryStatus
2025-11-15 A_BLEOffBeforeEpaperRefresh
2025-11-15 ChangesInStatus
2025-11-15 AF_FirmwareNoUpdate
2025-11-15 APK_generated
2025-11-16 F_NewButton
2025-11-16 F_3barbuttonImage
2025-11-16 F_textModified
2025-11-16 F_InframeFit
2025-11-17 APK_Release
2025-11-17 JLCPCB
2025-11-25 Pexels added
2025-11-25 F_URLAdded
2025-11-25 F_buttonNameChange
2025-11-26 F_InappLogoChange
2025-11-26 F_APKMade
2025-11-26 F_AI buttons
2025-11-26 F_AI_Buttons
2025-11-26 F_WaitingLines
2025-11-26 F_Gdrive
2025-11-26 F_tab_Adjustment
2025-11-26 F_CanvasBtButtonAdded
2025-11-26 F_ButtonSelection
2025-11-26 F_chnageInInstructions
2025-11-26 F_AutoRefreshCanvasBT
2025-11-27 F_Spelling
2025-11-27 F_smallChnages
2025-11-27 F_catagoryArrangement
2025-11-27 F_CanvasBTButtonsRename
2025-11-27 F_Renaming
2025-12-01 F_SameFont
2025-12-01 F_buttonsfontSame
2025-12-01 F_backUseInEdittor
2025-12-01 F_ExitButtonRemoved
2025-12-01 F_buttonsColours
2025-12-01 F_textChange
2025-12-01 F_Vibrant
2025-12-01 F_hamburgerButton
2025-12-01 F_ButtonsAllignment
2025-12-02 F_buttons
2025-12-02 F_smallChanges
2025-12-02 F_OTAGDRIVE
2025-12-02 F_GdriveOTA
2025-12-02 FA_OTAWorking
2025-12-03 F_OTA
2025-12-03 F_OTAStable
2025-12-03 F_OTAFolderDeleted
2025-12-03 F_textInTroubleshoot
2025-12-03 F_FirstRunBleFixed
2025-12-03 A_StopingSleep.
2025-12-03 FA_CalibrationAlert
2025-12-03 F_Troubleshootmessage
2025-12-04 F_LEDIndicator
2025-12-04 F_BatteryStatus
2025-12-04 A_BatteryFix
2025-12-04 F_SkipButtonAdded
2025-12-04 A_FimwareNumberUpdate
2025-12-04 F_CropeimageFix
2025-12-04 F_croppedImageFix
2025-12-04 F_ChargingStatusRemoved
2025-12-04 F_AlwaysSaveEnable
2025-12-04 Ready of ABB
2025-12-10 F_AIReportContent
2025-12-11 F_NoURL
2025-12-11 F_WithURL
2025-12-11 F_ReportButton
2025-12-11 F_modifiedReportbutton
2025-12-11 F_ReportModification
2025-12-11 F_ThankyouMessage
2025-12-11 F_SmallFixes
2025-12-11 F_FewSmallChanges
2025-12-11 F_MessageAgain
2026-01-15 A_AppUpload
2026-01-15 A_Updated_Readme

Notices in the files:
parts and their libraries:
SparkFun-Jumpers: Licensing: Creative Commons ShareAlike 4.0 International - https://creativecommons.org/licenses/by-sa/4.0
microbuilder: This work is placed in the public domain, and may be freely used for commercial and non-commercial work with the following conditions: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
